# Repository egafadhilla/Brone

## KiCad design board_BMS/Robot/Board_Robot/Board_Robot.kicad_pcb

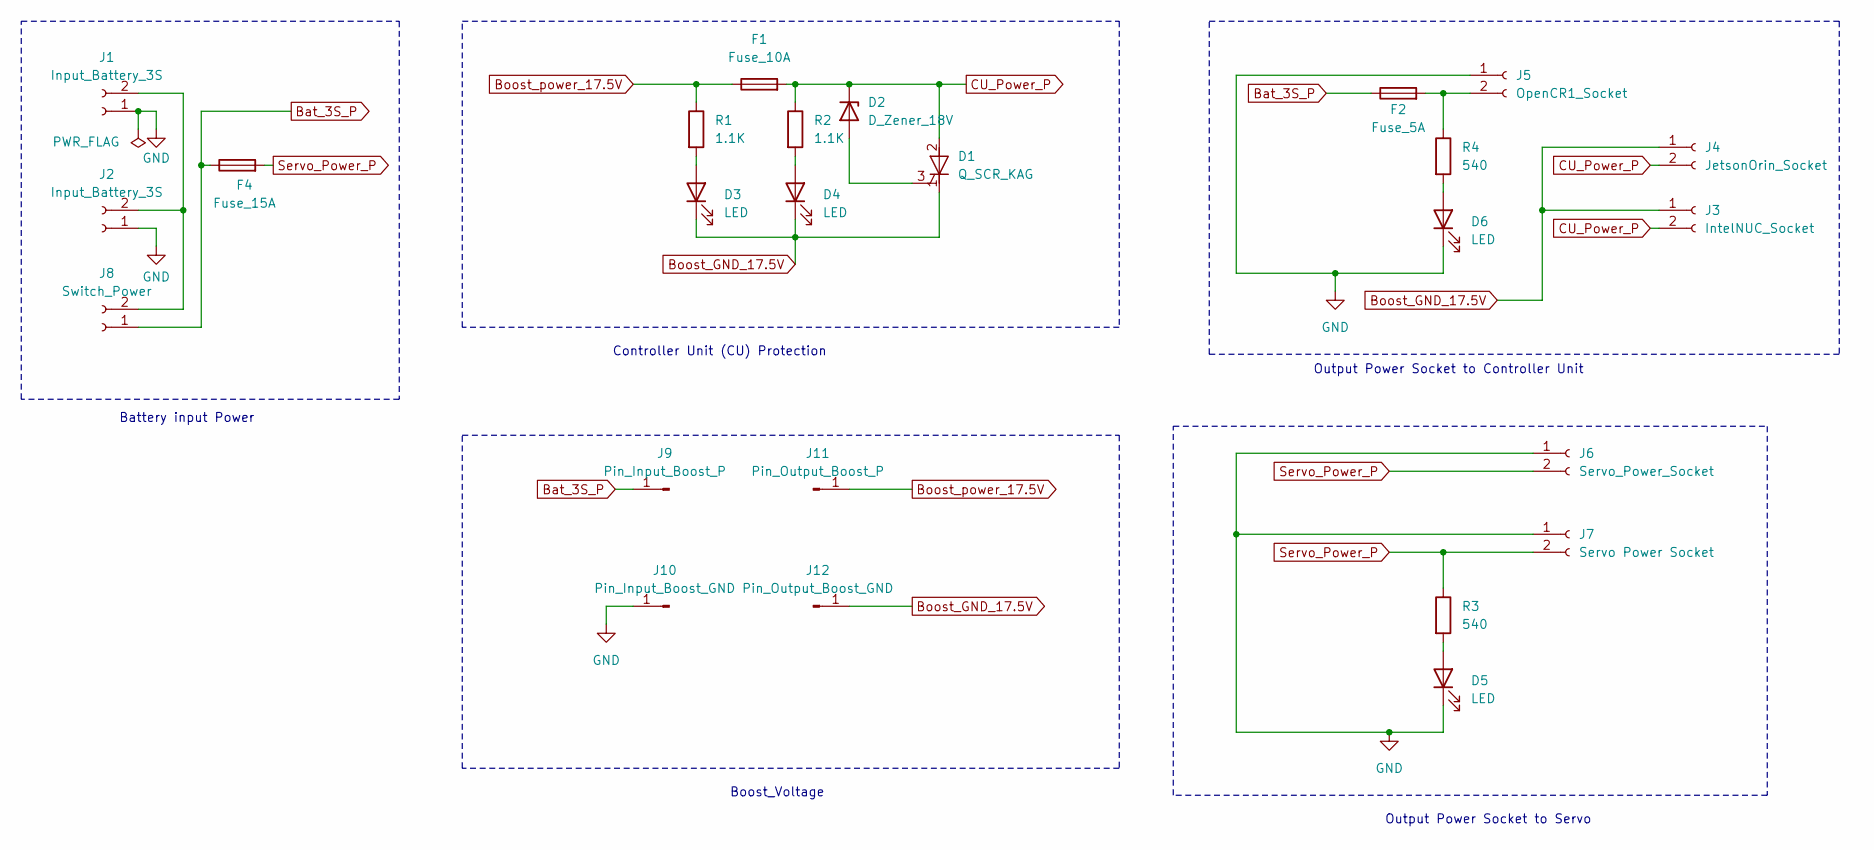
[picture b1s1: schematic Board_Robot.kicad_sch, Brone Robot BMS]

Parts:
D1: Q_SCR_KAG; TO-252-2
D2: D_Zener_18V; Nexperia_CFP3_SOD-123W
D3, D4, D5, D6: LED; LED_1206_3216Metric_Pad1.42x1.75mm_HandSolder
F1: Fuse_10A; C_1808_4520Metric_Pad1.72x2.30mm_HandSolder
F2: Fuse_5A; C_1808_4520Metric_Pad1.72x2.30mm_HandSolder
F4: Fuse_15A; C_1808_4520Metric_Pad1.72x2.30mm_HandSolder
J1, J2: Input_Battery_3S; xt60pw_m
J3: IntelNUC_Socket; XT30PW_M
J4: JetsonOrin_Socket; XT30PW_M
J5: OpenCR1_Socket; XT30PW_M
J6: Servo_Power_Socket; xt60pw_m
J7: Servo Power Socket; xt60pw_m
J8: Switch_Power; XT30PW_M
J9: Pin_Input_Boost_P; PinHeader_1x01_P2.54mm_Vertical
J10: Pin_Input_Boost_GND; PinHeader_1x01_P2.54mm_Vertical
J11: Pin_Output_Boost_P; PinHeader_1x01_P2.54mm_Vertical
J12: Pin_Output_Boost_GND; PinHeader_1x01_P2.54mm_Vertical
R1, R2: 1.1K; R_1206_3216Metric_Pad1.30x1.75mm_HandSolder
R3, R4: 540; R_1206_3216Metric_Pad1.30x1.75mm_HandSolder

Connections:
Bat_3S_P: F2.1, F4.1, J8.1, J9.1 (Pin_1_1)
Boost_GND_17.5V: D1.1 (K), D3.1 (K), D4.1 (K), J3.1, J4.1, J12.1 (Pin_1_1)
Boost_power_17.5V: F1.1, J11.1 (Pin_1_1), R1.1
CU_Power_P: D1.2 (A), D2.1 (K), F1.2, J3.2, J4.2, R2.1
GND: D5.1 (K), D6.1 (K), J1.1, J2.1, J5.1, J6.1, J7.1, J10.1 (Pin_1_1)
unnamed: D1.3 (G), D2.2 (A)
unnamed: D3.2 (A), R1.2
unnamed: D4.2 (A), R2.2
unnamed: D5.2 (A), R3.2
unnamed: D6.2 (A), R4.2
unnamed: J1.2, J2.2, J8.2
unnamed: F2.2, J5.2, R4.1
Servo_Power_P: F4.2, J6.2, J7.2, R3.1

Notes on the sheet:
Boost_Voltage
Battery input Power
Output Power Socket to Controller Unit
Output Power Socket to Servo
Controller Unit (CU) Protection

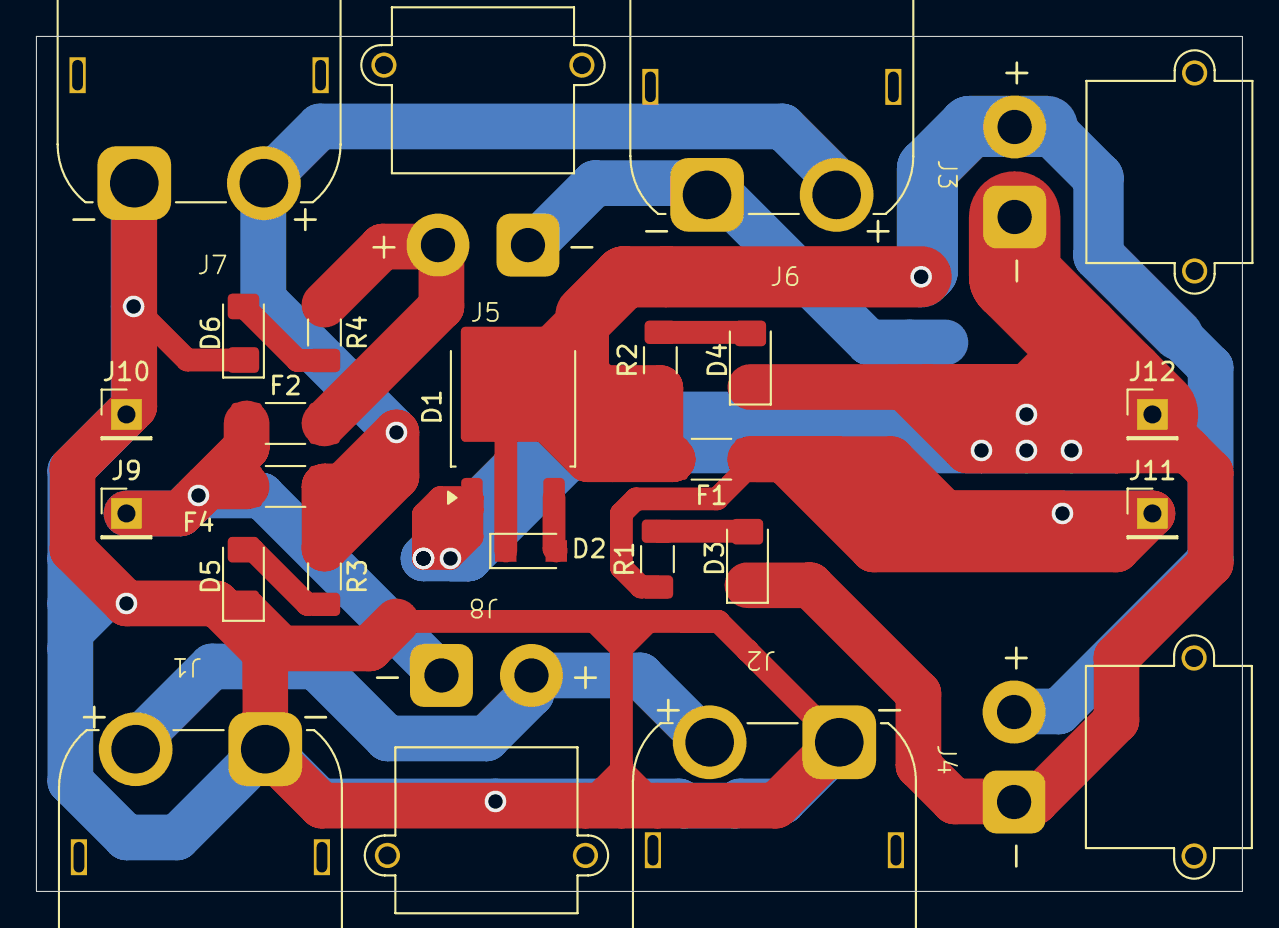
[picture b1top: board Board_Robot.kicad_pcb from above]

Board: 2 copper layers, 67.0 x 47.5 mm, 25 parts (0 on the bottom side), 13 nets.

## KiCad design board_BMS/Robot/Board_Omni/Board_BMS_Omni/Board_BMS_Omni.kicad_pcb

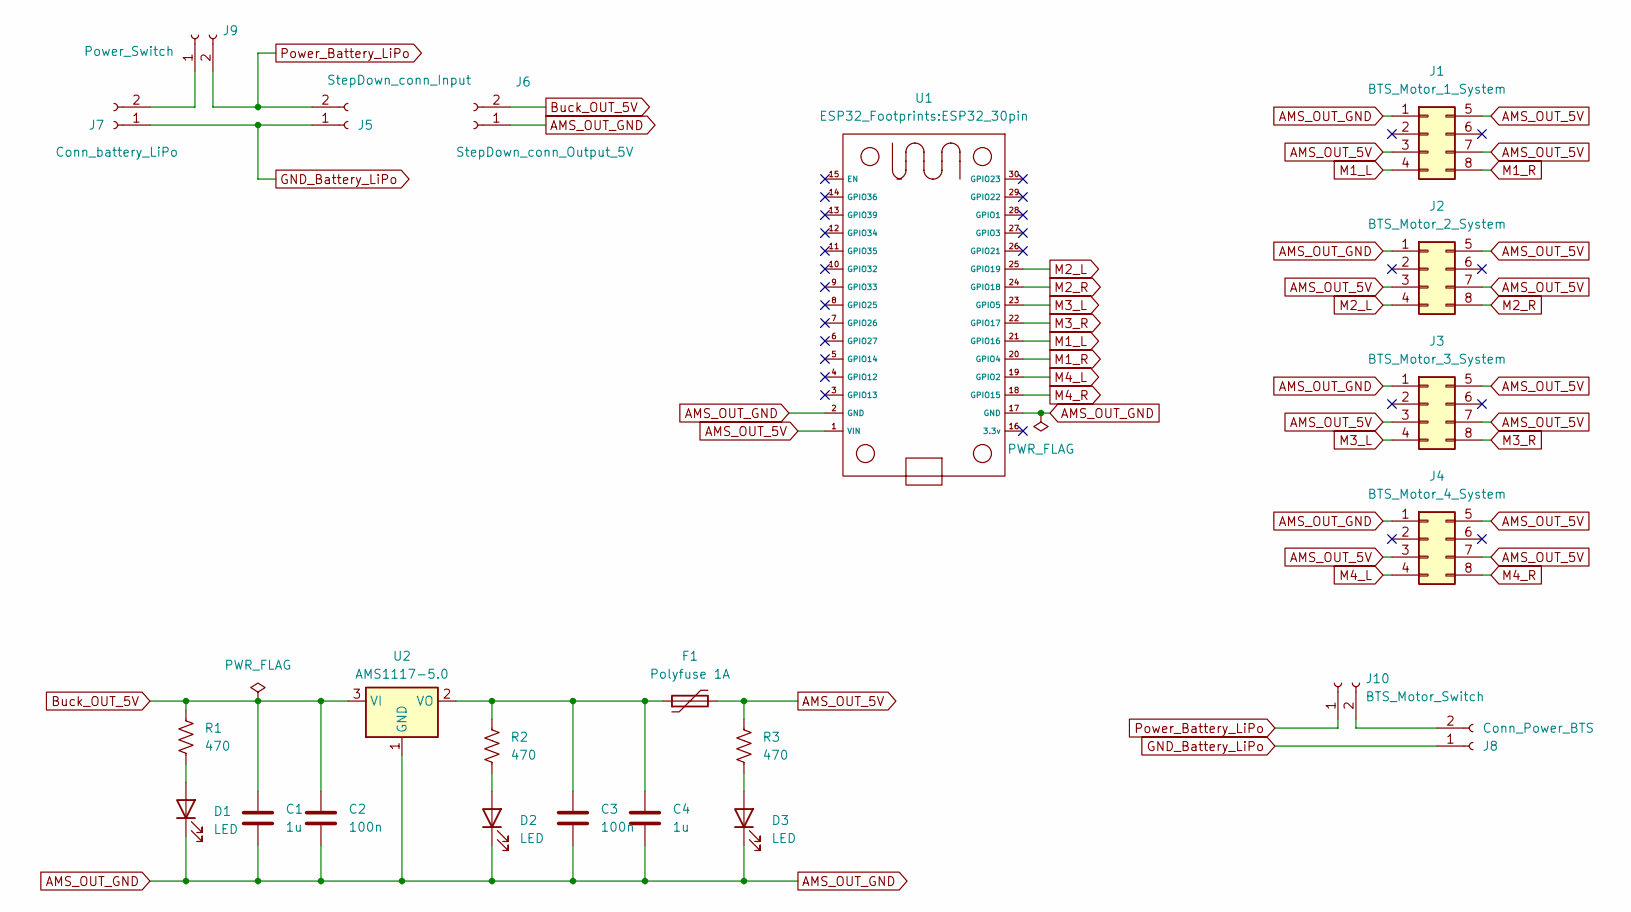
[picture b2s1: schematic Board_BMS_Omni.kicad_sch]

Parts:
C1, C4: 1u; C_1206_3216Metric_Pad1.33x1.80mm_HandSolder
C2, C3: 100n; C_1206_3216Metric_Pad1.33x1.80mm_HandSolder
D1, D2, D3: LED; LED_1206_3216Metric_Pad1.42x1.75mm_HandSolder
F1: Polyfuse 1A; 1206
J1: BTS_Motor_1_System; PinHeader_2x04_P2.54mm_Vertical
J2: BTS_Motor_2_System; PinHeader_2x04_P2.54mm_Vertical
J3: BTS_Motor_3_System; PinHeader_2x04_P2.54mm_Vertical
J4: BTS_Motor_4_System; PinHeader_2x04_P2.54mm_Vertical
J5: StepDown_conn_Input; PinHeader_1x02_P1.00mm_Vertical
J6: StepDown_conn_Output_5V; PinHeader_1x02_P1.00mm_Vertical
J7: Conn_battery_LiPo; AMASS_XT60PW-M_1x02_P7.20mm_Horizontal
J8: Conn_Power_BTS; AMASS_XT60PW-M_1x02_P7.20mm_Horizontal
J9: Power_Switch; AMASS_XT60PW-M_1x02_P7.20mm_Horizontal
J10: BTS_Motor_Switch; AMASS_XT60PW-M_1x02_P7.20mm_Horizontal
R1, R2, R3: 470; R_1206_3216Metric
U1: ESP32_30pin
U2: AMS1117-5.0; SOT-223-3_TabPin2

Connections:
AMS_OUT_5V: F1.2, J1.3, J1.5, J1.7, J2.3, J2.5, J2.7, J3.3, J3.5, J3.7, J4.3, J4.5, J4.7, R3.1, U1.1 (VIN)
AMS_OUT_GND: C1.2, C2.2, C3.2, C4.2, D1.1 (K), D2.1 (K), D3.1 (K), J1.1, J2.1, J3.1, J4.1, J6.1, U1.2 (GND), U1.17 (GND), U2.1 (GND)
Buck_OUT_5V: C1.1, C2.1, J6.2, R1.1, U2.3 (VI)
GND_Battery_LiPo: J5.1, J7.1, J8.1
M1_L: J1.4, U1.21 (GPIO16)
M1_R: J1.8, U1.20 (GPIO4)
M2_L: J2.4, U1.25 (GPIO19)
M2_R: J2.8, U1.24 (GPIO18)
M3_L: J3.4, U1.23 (GPIO5)
M3_R: J3.8, U1.22 (GPIO17)
M4_L: J4.4, U1.19 (GPIO2)
M4_R: J4.8, U1.18 (GPIO15)
unnamed: D1.2 (A), R1.2
unnamed: D2.2 (A), R2.2
unnamed: D3.2 (A), R3.2
unnamed: J7.2, J9.1
unnamed: J8.2, J8.4, J10.2, J10.3
unnamed: C3.1, C4.1, F1.1, R2.1, U2.2 (VO)
Power_Battery_LiPo: J5.2, J9.2, J10.1

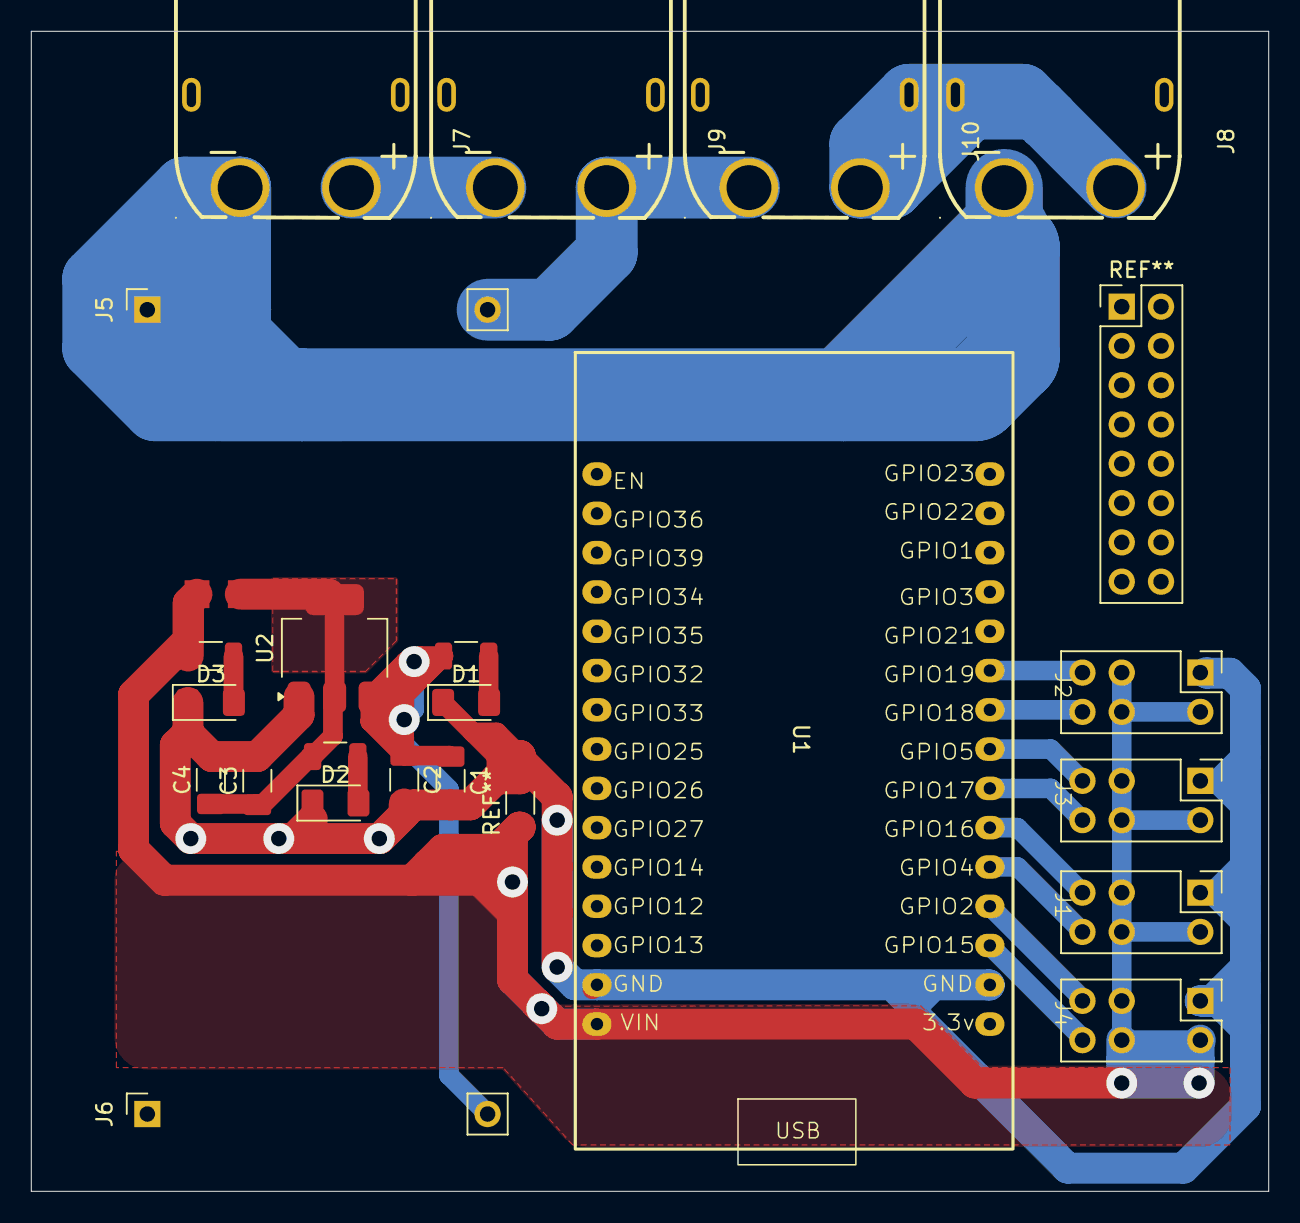
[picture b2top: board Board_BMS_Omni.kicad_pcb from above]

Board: 2 copper layers, 80.0 x 75.0 mm, 23 parts (0 on the bottom side), 19 nets.
